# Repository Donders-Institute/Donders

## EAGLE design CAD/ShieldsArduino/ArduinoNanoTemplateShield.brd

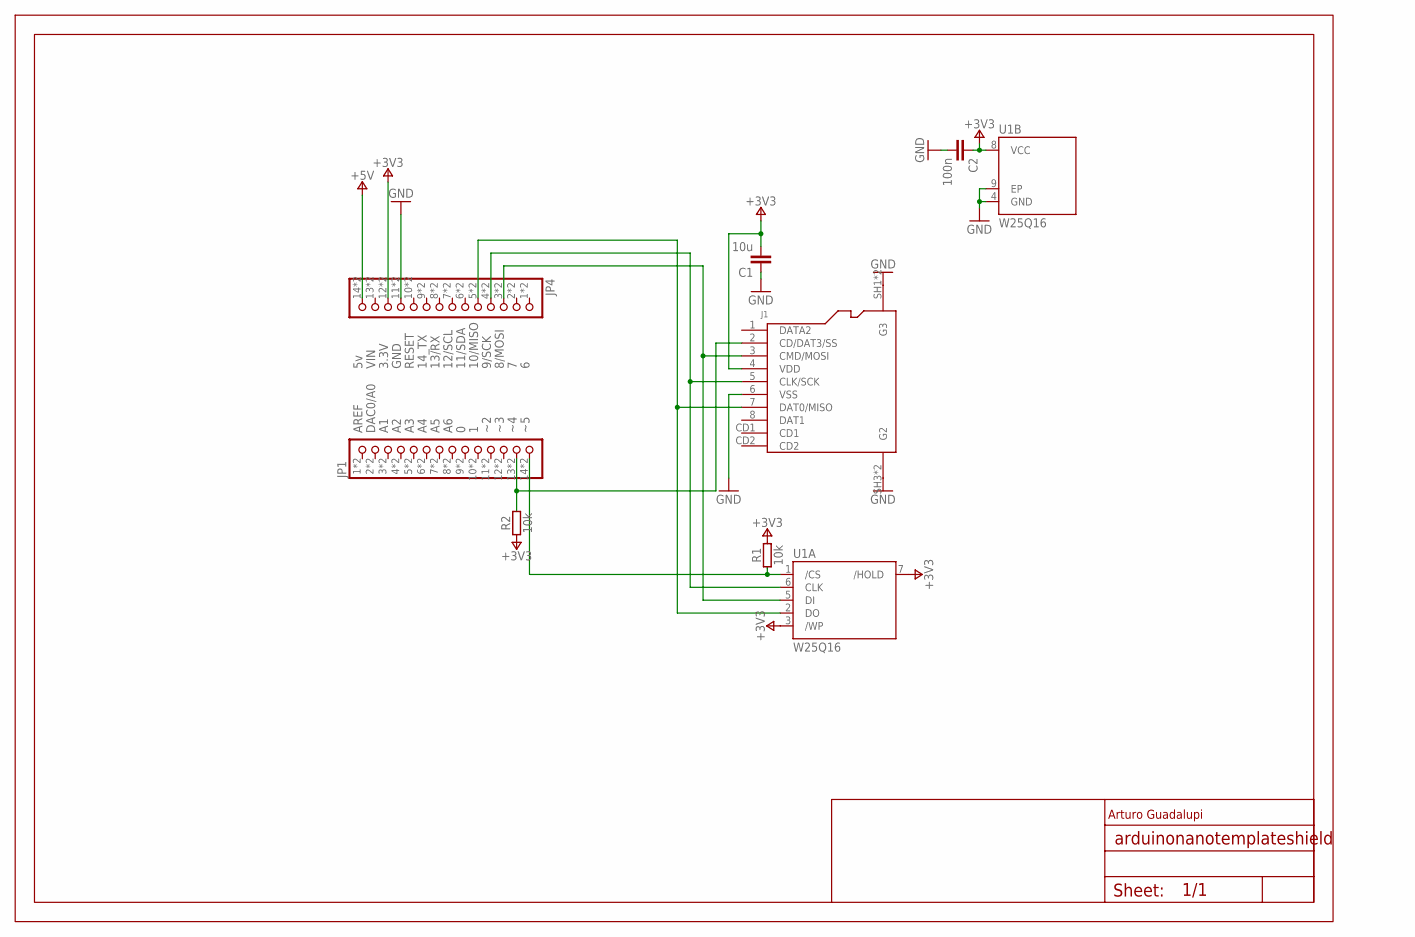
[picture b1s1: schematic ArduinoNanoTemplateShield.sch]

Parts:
C1: 10u; 0603-1608X90N
C2: 100n; 0603-1608X90N
FRAME1: DNP; FRAME
J1: -; AMPHENOL_114-00841-68
JP1, JP4: -; 1X14-DOUBLE
R1, R2: 10k; C0603
U1: W25Q16; SON9P127_500X600X80L60X41T340X400N

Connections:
+3V3: C1.2, C2.1, J1.4 (VDD), JP4.12, JP4.26 (12), R1.2, R2.1, U1.3 (/WP), U1.7 (/HOLD), U1.8 (VCC)
+5V: JP4.14, JP4.28 (14)
GND: C1.1, C2.2, J1.6 (VSS), J1.SH1 (G3), J1.SH2 (G3), J1.SH3 (G2), J1.SH4 (G2), JP4.11, JP4.25 (11), U1.4 (GND), U1.9 (EP)
unnamed: JP1.14, JP1.28 (14), R1.1, U1.1 (/CS)
unnamed: J1.3 (CMD/MOSI), JP4.3, JP4.17 (3), U1.5 (DI)
unnamed: J1.5 (CLK/SCK), JP4.4, JP4.18 (4), U1.6 (CLK)
unnamed: J1.7 (DAT0/MISO), JP4.5, JP4.19 (5), U1.2 (DO)
unnamed: J1.2 (CD/DAT3/SS), JP1.13, JP1.27 (13), R2.2

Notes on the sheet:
AREF
DAC0/A0
8/MOSI
9/SCK
10/MISO
11/SDA
12/SCL
13/RX
14_TX
RESET
GND
3.3V
VIN
Arturo Guadalupi

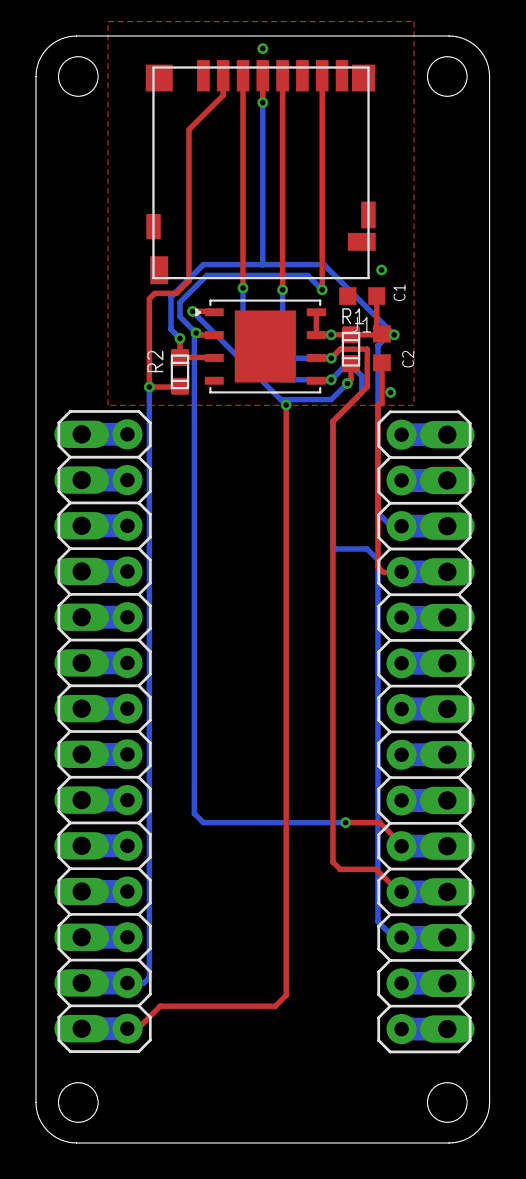
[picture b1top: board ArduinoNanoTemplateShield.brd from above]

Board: 2 copper layers, 25.2 x 61.5 mm, 9 parts (0 on the bottom side), 8 nets.

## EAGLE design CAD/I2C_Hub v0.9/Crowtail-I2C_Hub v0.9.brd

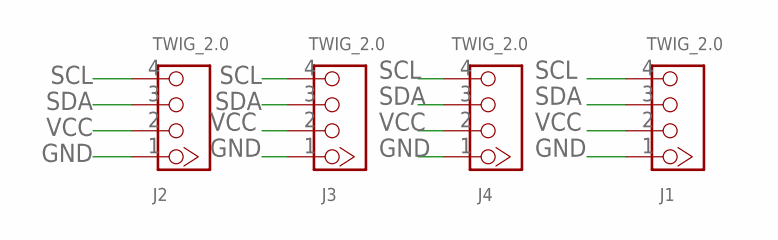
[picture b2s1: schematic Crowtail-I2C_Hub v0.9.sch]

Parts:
J1, J2, J3, J4: TWIG_2.0; 2.0_1X4

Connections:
GND: J1.1, J2.1, J3.1, J4.1
SCL: J1.4, J2.4, J3.4, J4.4
SDA: J1.3, J2.3, J3.3, J4.3
VCC: J1.2, J2.2, J3.2, J4.2

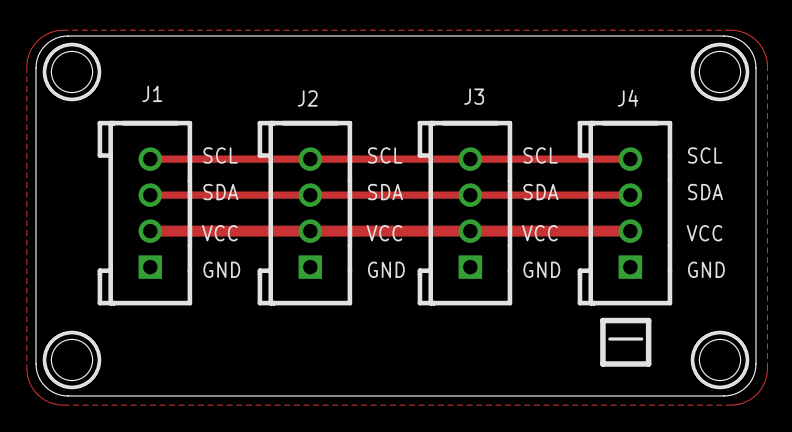
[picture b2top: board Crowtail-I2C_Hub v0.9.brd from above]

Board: 2 copper layers, 40.0 x 20.0 mm, 4 parts (0 on the bottom side), 4 nets.

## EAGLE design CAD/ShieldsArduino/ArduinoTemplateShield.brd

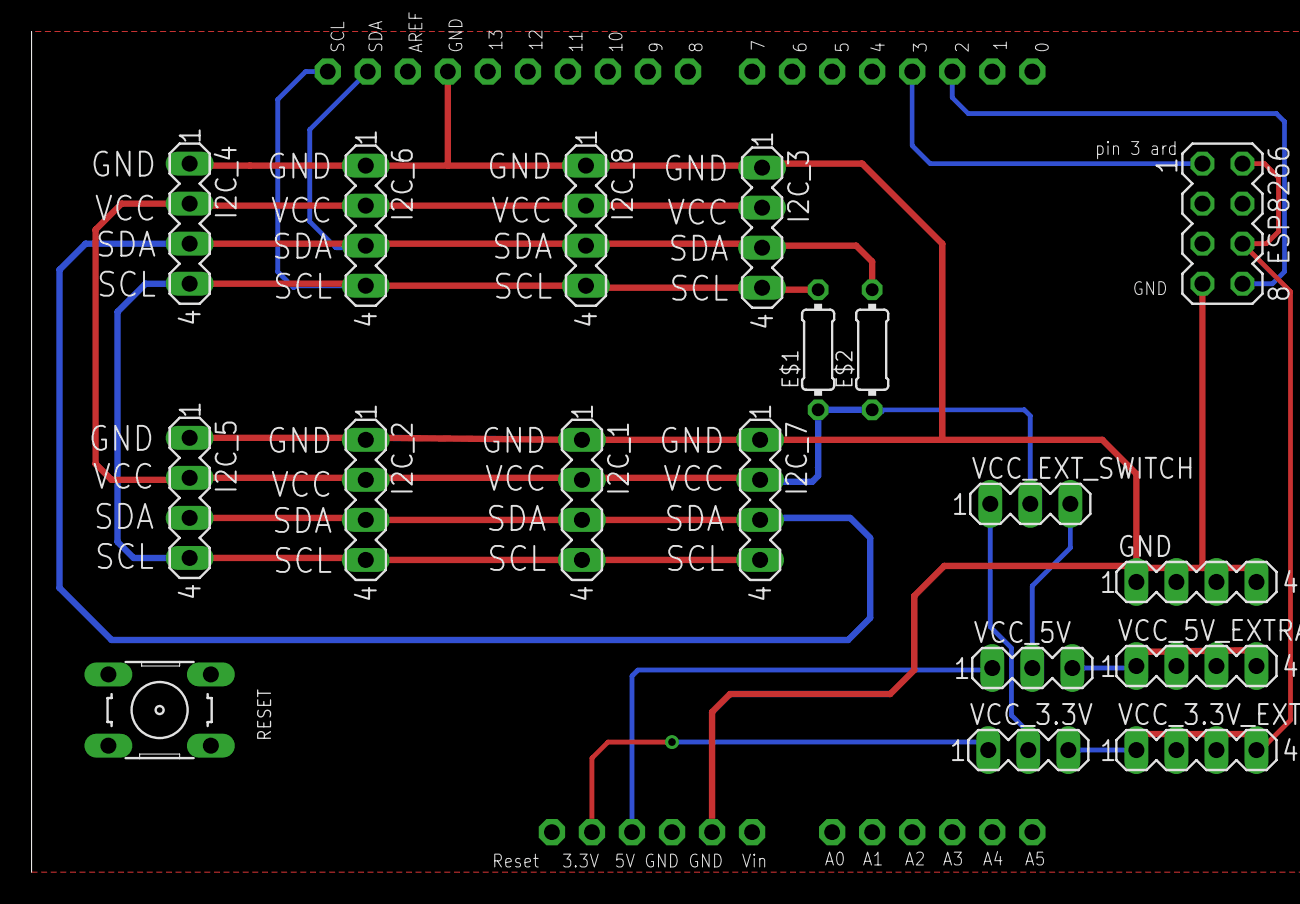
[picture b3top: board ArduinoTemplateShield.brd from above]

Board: 2 copper layers, 19 parts (0 on the bottom side), 12 nets.

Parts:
E$1, E$2: 0204/7
ESP8266: MA04-2
GND: MA04-1
I2C_1, I2C_2, I2C_3, I2C_4, I2C_5, I2C_6, I2C_7, I2C_8: MA04-1
RESET: B3F-10XX
U1: ARDUINOR3-NOIOREF-NOTEXT; ARDUINOR3-NOTEXT-NOIOREF
VCC_3.3V, VCC_5V: MA03-1
VCC_3.3V_EXTRA, VCC_5V_EXTRA: MA04-1
VCC_EXT_SWITCH: MA03-1

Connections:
S$1: VCC_5V.3, VCC_5V_EXTRA.1
S$2: VCC_3.3V.3, VCC_3.3V_EXTRA.1
S$3: ESP8266.2, ESP8266.6, VCC_3.3V_EXTRA.4
S$5: U1.5V, VCC_5V.1
S$6: I2C_6.4, U1.SCL
S$7: I2C_6.3, U1.SDA
S$8: ESP8266.1, U1.D3
S$12: VCC_5V.2, VCC_EXT_SWITCH.3
S$13: U1.3V, VCC_3.3V.1
S$14: VCC_3.3V.2, VCC_EXT_SWITCH.1
S$15: ESP8266.8, U1.D2
VCC_EXT: E$2.1, VCC_EXT_SWITCH.2

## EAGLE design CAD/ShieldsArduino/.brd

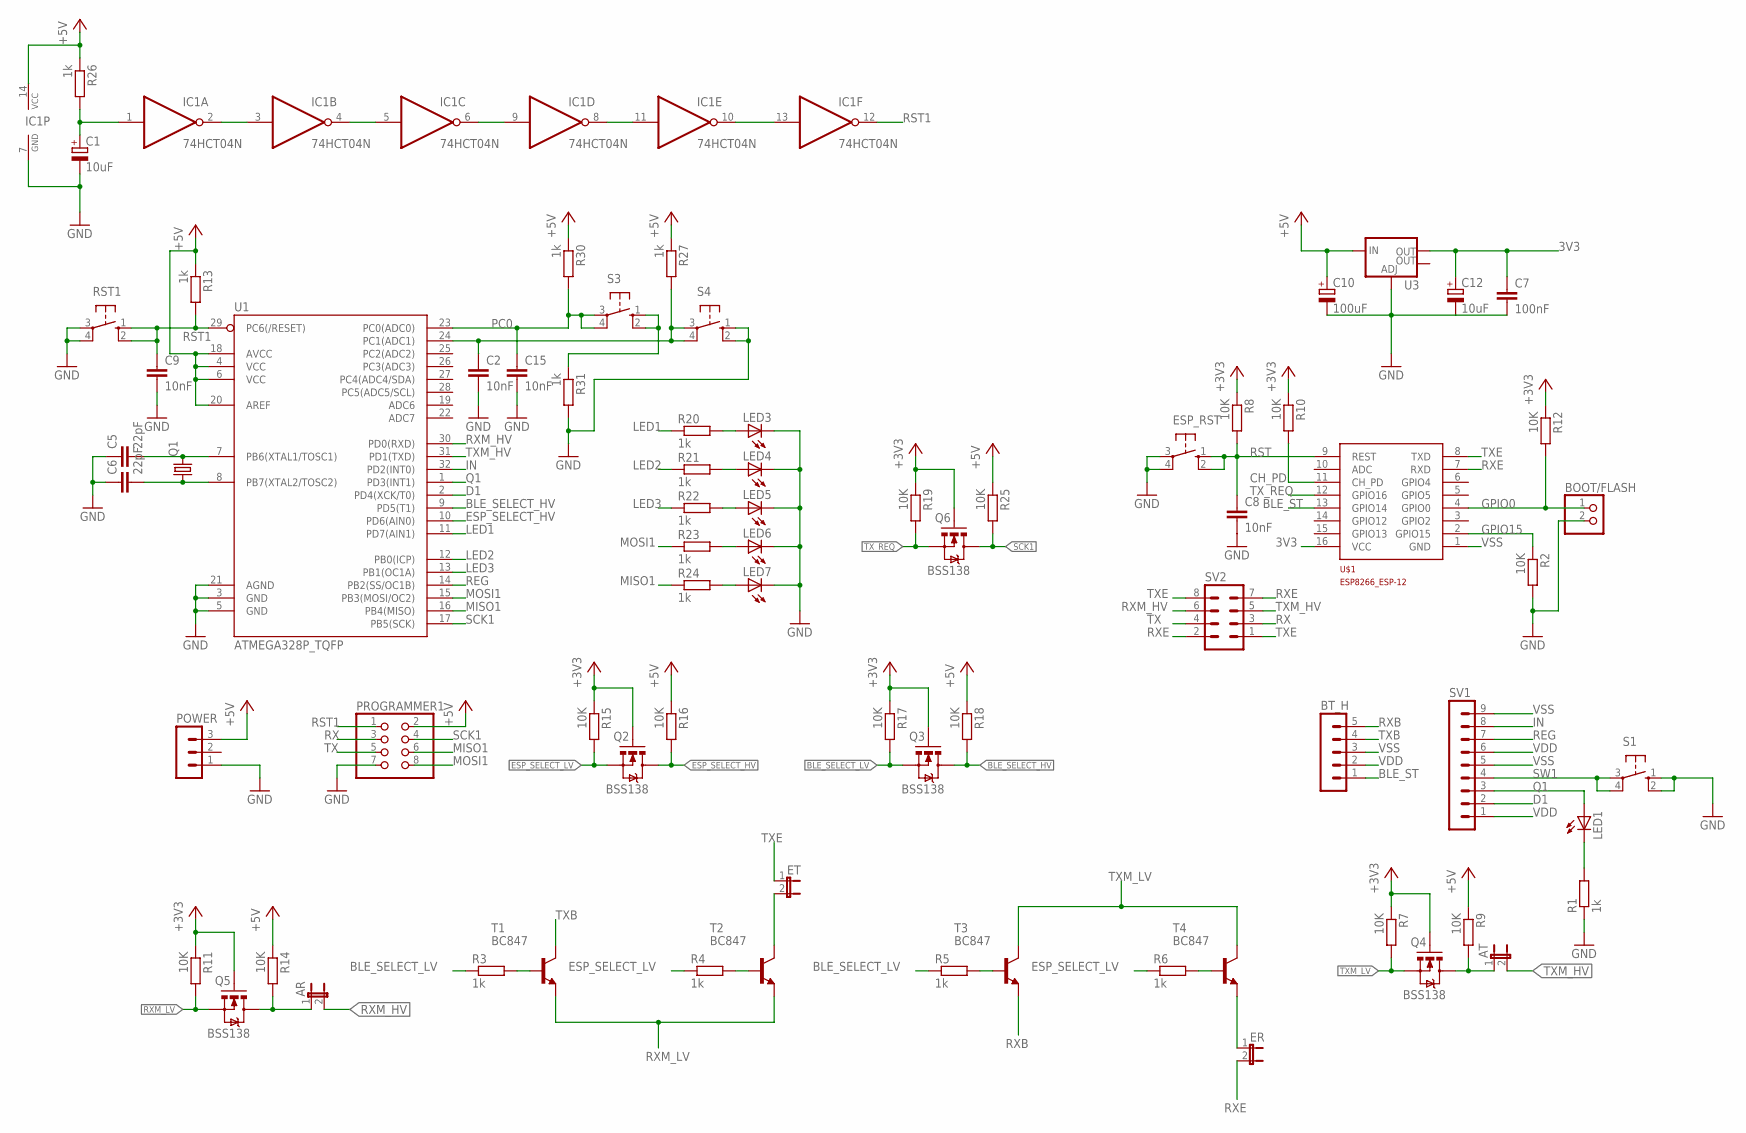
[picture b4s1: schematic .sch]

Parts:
AR: JP1E; JP1
AT: JP1E; JP1
BOOT/FLASH: PINHD-1X2; 1X02
BT_H: MA05-1
C1, C12: 10uF; 153CLV-0405
C2, C8, C9, C15: 10nF; C1206
C5, C6: 22pF; C1206
C7: 100nF; C1206
C10: 100uF; 153CLV-0605
ER: JP1E; JP1
ESP_RST: 10-XX; B3F-10XX
ET: JP1E; JP1
IC1: 74HCT04N; DIL14
LED1, LED3, LED4, LED5, LED6, LED7: LED5MM
POWER: MA03-1
PROGRAMMER1: PINHD-2X4; 2X04
Q1: CRYSTALHC49UP; HC49UP
Q2, Q3, Q4, Q5, Q6: BSS138; SOT23-3
R1, R3, R4, R5, R6, R13, R20, R21, R22, R23, R24, R26, R27, R30, R31: 1k; R1206
R2, R7, R8, R9, R10, R11, R12, R14, R15, R16, R17, R18, R19, R25: 10K; R1206
RST1: 10-XX; B3F-10XX
S1, S3, S4: 40-XX; B3F-40XX
SV1: MA09-1
SV2: MA04-2
T1, T2, T3, T4: BC847; SOT23
U1: ATMEGA328P_TQFP; TQFP32-08
U3: V_REG_LM1117SOT223; SOT223
U$1: ESP8266_ESP-12; ESP8266-ESP12

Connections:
3V3: C7.1, C12.+, Q2.1 (G), Q3.1 (G), Q4.1 (G), Q5.1 (G), Q6.1 (G), R7.1, R8.1, R10.1, R11.1, R12.1, R15.1, R17.1, R19.1, U3.2 (OUT), U$1.16 (VCC)
BLE_SELECT_HV: Q3.3 (D), R18.2, U1.9 (PD5(T1))
BLE_SELECT_LV: Q3.2 (S), R3.1, R5.1, R17.2
BLE_ST: BT_H.1, U$1.13 (GPIO14)
CH_PD: R10.2, U$1.11 (CH_PD)
D1: SV1.2, U1.2 (PD4(XCK/T0))
ESP_SELECT_HV: Q2.3 (D), R16.2, U1.10 (PD6(AIN0))
ESP_SELECT_LV: Q2.2 (S), R4.1, R6.1, R15.2
GPIO0: BOOT/FLASH.1, R12.2, U$1.4 (GPIO0)
GPIO15: R2.1, U$1.2 (GPIO15)
IN: SV1.8, U1.32 (PD2(INT0))
LED1: R20.1, U1.11 (PD7(AIN1))
LED2: R21.1, U1.12 (PB0(ICP))
LED3: R22.1, U1.13 (PB1(OC1A))
MISO1: PROGRAMMER1.6, R24.1, U1.16 (PB4(MISO))
MOSI1: PROGRAMMER1.8, R23.1, U1.15 (PB3(MOSI/OC2))
unnamed: R3.2, T1.1 (B)
unnamed: R4.2, T2.1 (B)
unnamed: R5.2, T3.1 (B)
unnamed: IC1.2 (O), IC1.3 (I)
unnamed: LED1.K (C), R1.2
unnamed: R6.2, T4.1 (B)
unnamed: IC1.4 (O), IC1.5 (I)
unnamed: IC1.6 (O), IC1.9 (I)
unnamed: IC1.8 (O), IC1.11 (I)
unnamed: IC1.10 (O), IC1.13 (I)
unnamed: C1.+, IC1.1 (I), R26.2
unnamed: C5.2, Q1.2, U1.7 (PB6(XTAL1/TOSC1))
unnamed: C2.1, R27.2, S4.3, S4.4 (P1), U1.24 (PC1(ADC1))
unnamed: C6.2, Q1.1, U1.8 (PB7(XTAL2/TOSC2))
unnamed: LED3.A, R20.2
unnamed: LED4.A, R21.2
unnamed: LED5.A, R22.2
unnamed: LED6.A, R23.2
unnamed: LED7.A, R24.2
unnamed: R31.1, S3.1 (S), S3.2 (S1)
PC0: C15.1, R30.2, S3.3, S3.4 (P1), U1.23 (PC0(ADC0))
Q1: LED1.A, SV1.3, U1.1 (PD3(INT1))
REG: SV1.7, U1.14 (PB2(SS/OC1B))
RST: C8.1, ESP_RST.1 (S), ESP_RST.2 (S1), R8.2, U$1.9 (REST)
RST1: C9.1, IC1.12 (O), PROGRAMMER1.1, R13.2, RST1.1 (S), RST1.2 (S1), U1.29 (PC6(/RESET))
RX: PROGRAMMER1.3, SV2.3
RXB: BT_H.5, T3.2 (E)
RXE: ER.2, SV2.2, SV2.7, U$1.7 (RXD)
RXE_J: ER.1, T4.2 (E)
RXM_HV: AR.2, SV2.6, U1.30 (PD0(RXD))
RXM_HV_J: AR.1, Q5.3 (D), R14.2
RXM_LV: Q5.2 (S), R11.2, T1.2 (E), T2.2 (E)
SCK1: PROGRAMMER1.4, Q6.3 (D), R25.2, U1.17 (PB5(SCK))
SW1: S1.3, S1.4 (P1), SV1.4
TX: PROGRAMMER1.5, SV2.4
TXB: BT_H.4, T1.3 (C)
TXE: ET.1, SV2.1, SV2.8, U$1.8 (TXD)
TXE_J: ET.2, T2.3 (C)
TXM_HV: AT.2, SV2.5, U1.31 (PD1(TXD))
TXM_HV_J: AT.1, Q4.3 (D), R9.2
TXM_LV: Q4.2 (S), R7.2, T3.3 (C), T4.3 (C)
TX_REQ: Q6.2 (S), R19.2, U$1.12 (GPIO16)
VDD: BT_H.2, C10.+, IC1.14 (VCC), POWER.3, PROGRAMMER1.2, R9.1, R13.1, R14.1, R16.1, R18.1, R25.1, R26.1, R27.1, R30.1, SV1.1, SV1.6, U1.4 (VCC), U1.6 (VCC), U1.18 (AVCC), U1.20 (AREF), U3.3 (IN)
VSS: BOOT/FLASH.2, BT_H.3, C1.-, C2.2, C5.1, C6.1, C7.2, C8.2, C9.2, C10.-, C12.-, C15.2, ESP_RST.3, ESP_RST.4 (P1), IC1.7 (GND), LED3.K (C), LED4.K (C), LED5.K (C), LED6.K (C), LED7.K (C), POWER.1, PROGRAMMER1.7, R1.1, R2.2, R31.2, RST1.3, RST1.4 (P1), S1.1 (S), S1.2 (S1), S4.1 (S), S4.2 (S1), SV1.5, SV1.9, U1.3 (GND), U1.5 (GND), U1.21 (AGND), U3.1 (ADJ), U$1.1 (GND)

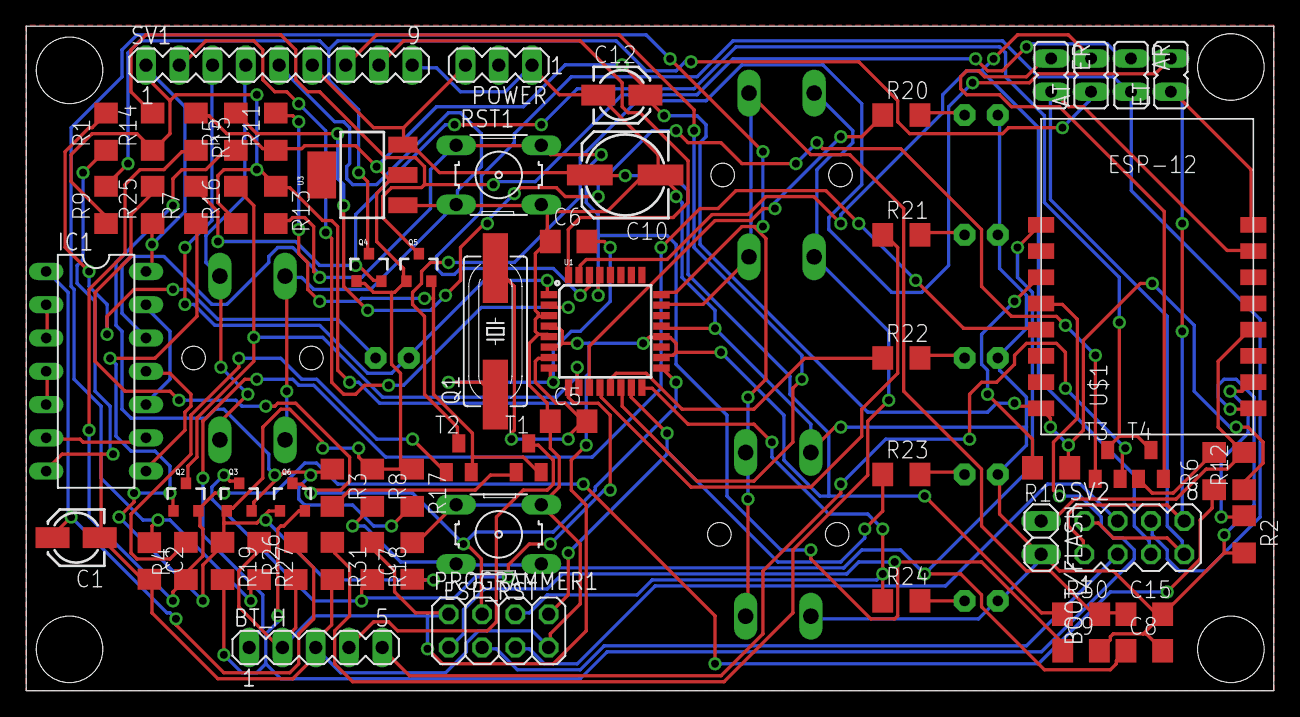
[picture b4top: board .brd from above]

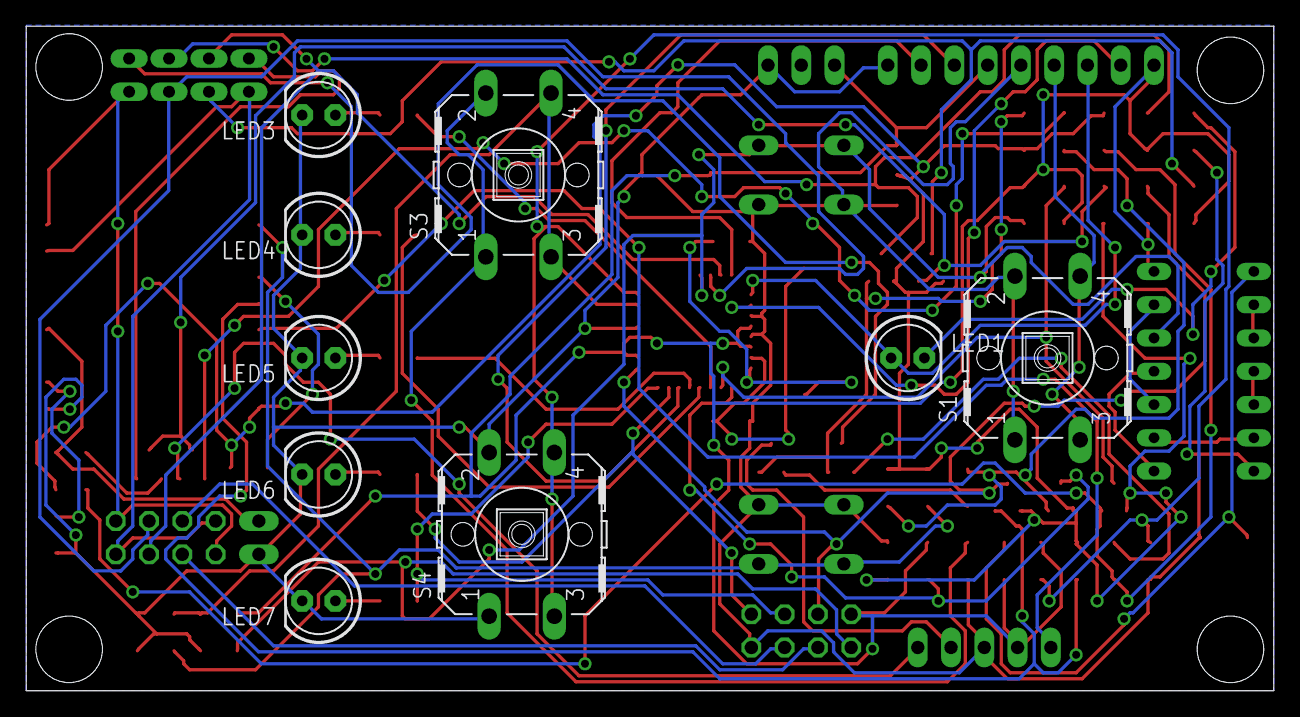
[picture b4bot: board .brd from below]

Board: 2 copper layers, 95.2 x 50.7 mm, 74 parts (9 on the bottom side), 60 nets.

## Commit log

2020-01-08 Create README.md
    Ini
2020-01-08 Migrating projects form gitlab.science.ru.nl to github
2020-01-08 Adding projects to Donders Repository

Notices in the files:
CAD/ShieldsArduino/ArduinoNanoTemplateShield.brd:
Copyright (c) 2016-2017 Arduino LLC.  All right reserved. EAGLE Design Rules
parts and their libraries:
SparkFun-DigitalIC: Licensing: Creative Commons ShareAlike 4.0 International - https://creativecommons.org/licenses/by-sa/4.0
Arduino-ICs: Copyright (c) 2016-2017 Arduino LLC.  All right reserved.
Arduino-utility: This file is licensed under : CC-SA-BY-NC
